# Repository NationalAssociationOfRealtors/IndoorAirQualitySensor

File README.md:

All development on the Indoor Air Quality sensor is now on its own repository [here](https://github.com/NationalAssociationOfRealtors/Touchstone).

This repo is left for historical records only.

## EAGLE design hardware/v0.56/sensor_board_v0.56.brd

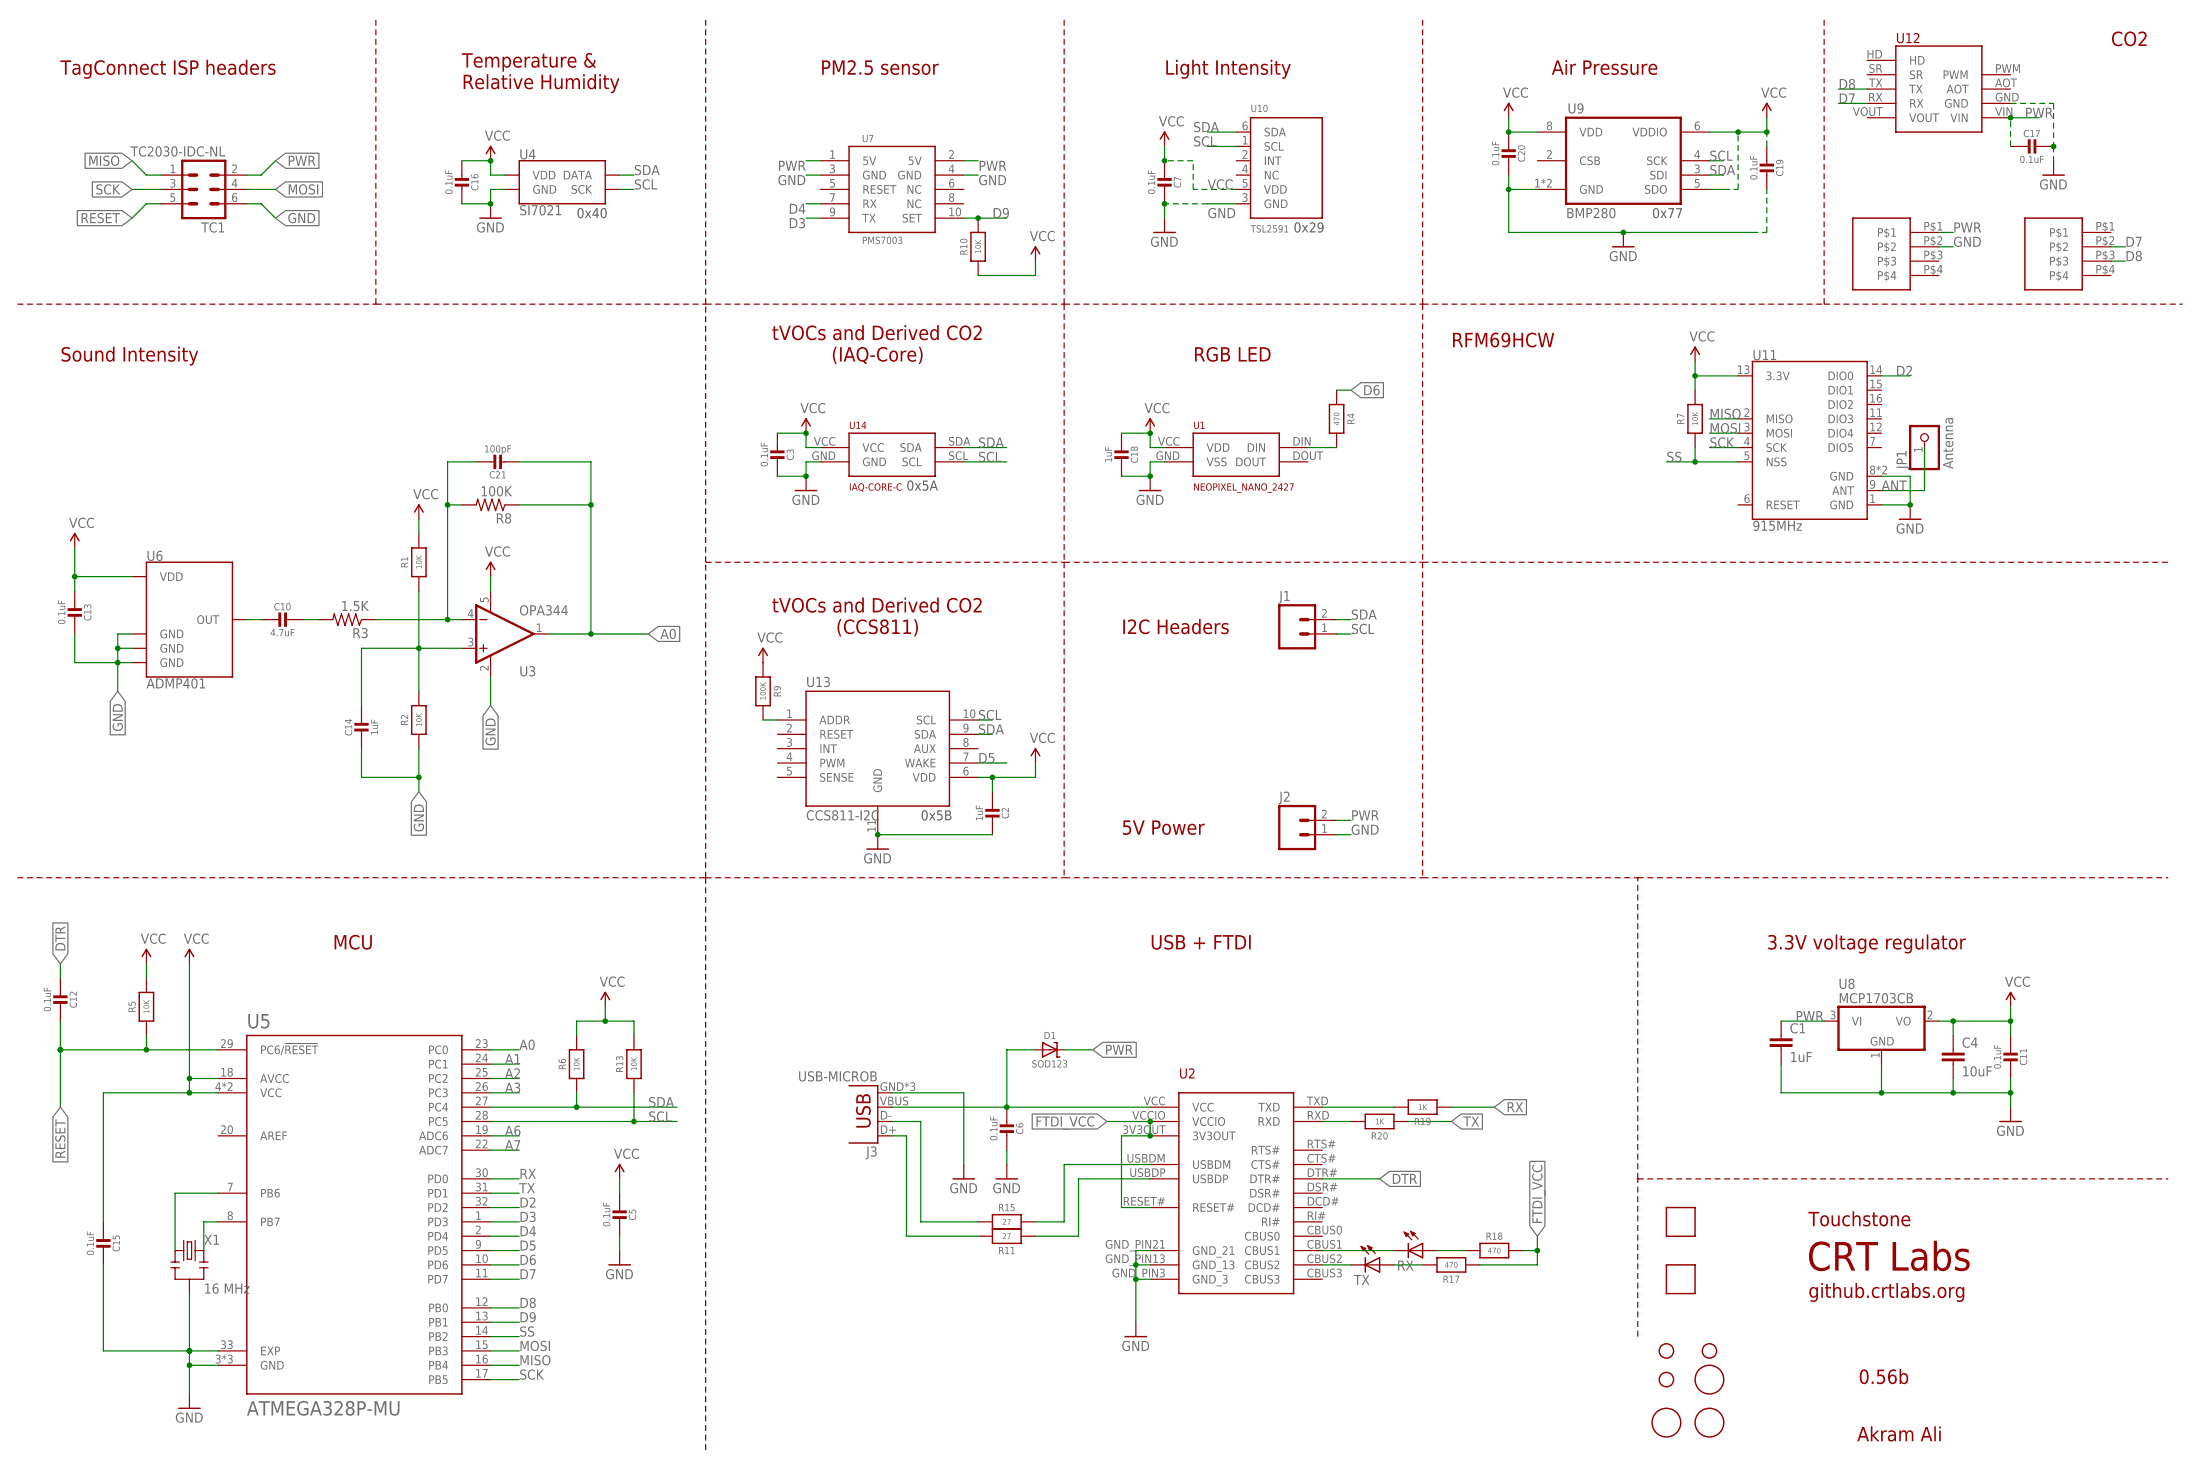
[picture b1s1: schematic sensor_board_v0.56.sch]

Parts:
C1: 1uF; 0805; MPN CC0805ZRY5V8BB105
C2, C14, C18: 1uF; MICROBUILDER__0402MP
C3, C5, C6, C7, C11, C12, C13, C15, C16, C17, C19, C20: 0.1uF; MICROBUILDER__0402MP
C4: 10uF; 0805; MPN CC0805KKX5R6BB106
C10: 4.7uF; MICROBUILDER__0402MP
C21: 100pF; MICROBUILDER__0402MP
D1: SOD123; MICROBUILDER_SOD-123
H1, H2, H3: STAND-OFF
J1, J2: M02PTH; 1X02
J3: USB-MICROB; MPN 47346-0001
JP1: Antenna; 1X01-CLEANBIG
R1, R2, R5, R6, R7, R10, R13: 10K; MICROBUILDER__0402MP
R3: 1.5K; 0805; MPN RC0805FR-071K5L
R4, R17, R18: 470; MICROBUILDER__0402MP
R8: 100K; 0805; MPN RC0805FR-07100KL
R9: 100K; MICROBUILDER__0402MP
R11, R15: 27; MICROBUILDER__0402MP
R19, R20: 1K; MICROBUILDER__0402MP
RX: LEDCHIPLED_0805; CHIPLED_0805; MPN LG R971-KN-1
TC1: TC2030-IDC-NL
TX: LEDCHIPLED_0805; CHIPLED_0805; MPN LG R971-KN-1
U1: NEOPIXEL_NANO_2427; SK6805-2427
U2: FT231XQ-R; FTDI_FT231XQ-R_PACKAGE
U3: OPA344; SOT23-5; MPN OPA344NA/3K
U4: SI7021; DFN-6-3X3-SI7021
U5: ATMEGA328P-MU; QFN50P500X500X100-33N
U6: ADMP401; MPN INMP401ACEZ-R7
U7: PMS7003; PMS7003_RECEPTACLE_1.27MM_2X5
U8: MCP1703CB; SOT23; MPN MCP1703T-2502E/CB
U9: BMP280; MPN BMP280
U10: TSL2591; DFN6_TAOS; MPN TSL25911FN
U11: 915MHz; RFM69HCW-XXXS2
U12: MH-Z19; MPN MH-z19
U13: CCS811-I2C; LGA
U14: IAQ-CORE-C
U15, U16: VLP-450-F
U$1, U$2, U$3: FIDUCIAL; FIDUCIAL_1MM
U$4, U$5: 0878980426; CONN_4POS_VERT_2.54_SMD
X1: 16 MHz; RESONATOR-SMD

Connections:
A0: C21.2, R8.1, U3.1 (OUT), U5.23 (PC0)
A1: U5.24 (PC1)
A2: U5.25 (PC2)
A3: U5.26 (PC3)
A6: U5.19 (ADC6)
A7: U5.22 (ADC7)
ANT: JP1.1, U11.9 (ANT)
D2: U5.32 (PD2), U11.14 (DIO0)
D3: U5.1 (PD3), U7.9 (TX)
D4: U5.2 (PD4), U7.7 (RX)
D5: U5.9 (PD5), U13.7 (WAKE)
D6: R4.1, U5.10 (PD6)
D7: U5.11 (PD7), U12.RX, U$5.P$2
D8: U5.12 (PB0), U12.TX, U$5.P$3
D9: R10.2, U5.13 (PB1), U7.10 (SET)
DTR: C12.2, U2.DTR#
FTDI_VCC: R17.1, R18.2, U2.3V3OUT, U2.RESET#, U2.VCCIO
GND: C1.2, C2.1, C3.1, C4.2, C5.1, C6.1, C7.1, C11.1, C13.1, C14.2, C15.1, C16.1, C17.1, C18.1, C19.1, C20.1, J2.1, J3.GND, J3.MT1 (GND), J3.MT2 (GND), R2.1, TC1.6, U1.GND (VSS), U2.GND_PIN3 (GND_3), U2.GND_PIN13 (GND_13), U2.GND_PIN21 (GND_21), U3.2 (V-), U4.GND, U5.3 (GND), U5.5 (GND), U5.21 (GND), U5.33 (EXP), U6.2 (GND), U6.4 (GND), U6.6 (GND), U7.3 (GND), U7.4 (GND), U8.1 (GND), U9.1 (GND), U9.7 (GND), U10.3 (GND), U11.1 (GND), U11.8 (GND), U11.10 (GND), U12.GND, U13.11 (GND), U14.GND, U$4.P$2, X1.2
MISO: TC1.1, U5.16 (PB4), U11.2 (MISO)
MOSI: TC1.4, U5.15 (PB3), U11.3 (MOSI)
unnamed: R4.2, U1.DIN
unnamed: R20.2, U2.RXD
unnamed: R19.2, U2.TXD
unnamed: U5.8 (PB7), X1.3
unnamed: U5.7 (PB6), X1.1
unnamed: C10.1, R3.2
unnamed: C21.1, R3.1, R8.2, U3.4 (-IN)
unnamed: C14.1, R1.1, R2.2, U3.3 (+IN)
unnamed: R9.2, U13.1 (ADDR)
unnamed: RX.C, U2.CBUS1
unnamed: TX.C, U2.CBUS2
unnamed: R15.2, U2.USBDM
unnamed: R11.1, U2.USBDP
unnamed: R18.1, RX.A
unnamed: R17.2, TX.A
unnamed: J3.D-, R15.1
unnamed: J3.D+, R11.2
OUT: C10.2, U6.1 (OUT)
PWR: C1.1, C17.2, D1.C, J2.2, TC1.2, U7.1 (5V), U7.2 (5V), U8.3 (VI), U12.VIN, U$4.P$1
RESET: C12.1, R5.1, TC1.5, U5.29 (PC6/!RESET)
RX: R19.1, U5.30 (PD0)
SCK: TC1.3, U5.17 (PB5), U11.4 (SCK)
SCL: J1.1, R13.1, U4.SCK, U5.28 (PC5), U9.4 (SCK), U10.1 (SCL), U13.10 (SCL), U14.SCL
SDA: J1.2, R6.1, U4.DATA, U5.27 (PC4), U9.3 (SDI), U10.6 (SDA), U13.9 (SDA), U14.SDA
SS: R7.1, U5.14 (PB2), U11.5 (NSS)
TX: R20.1, U5.31 (PD1)
VBUS: C6.2, D1.A, J3.VBUS, U2.VCC
VCC: C2.2, C3.2, C4.1, C5.2, C7.2, C11.2, C13.2, C15.2, C16.2, C18.2, C19.2, C20.2, R1.2, R5.2, R6.2, R7.2, R9.1, R10.1, R13.2, U1.VCC (VDD), U3.5 (V+), U4.VDD, U5.4 (VCC), U5.6 (VCC), U5.18 (AVCC), U6.5 (VDD), U8.2 (VO), U9.5 (SDO), U9.6 (VDDIO), U9.8 (VDD), U10.5 (VDD), U11.13 (3.3V), U13.6 (VDD), U14.VCC

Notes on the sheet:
Light Intensity
tVOCs and Derived CO2 (IAQ-Core)
Air Pressure
Sound Intensity
Temperature & Relative Humidity
TagConnect ISP headers
3.3V voltage regulator
CRT Labs
Touchstone
Akram Ali
USB + FTDI
0x5A
0x77
0.56b
github.crtlabs.org
0x29
RGB LED
I2C Headers
PM2.5 sensor
RFM69HCW
MCU
CO2
tVOCs and Derived CO2 (CCS811)
5V Power
0x5B
0x40

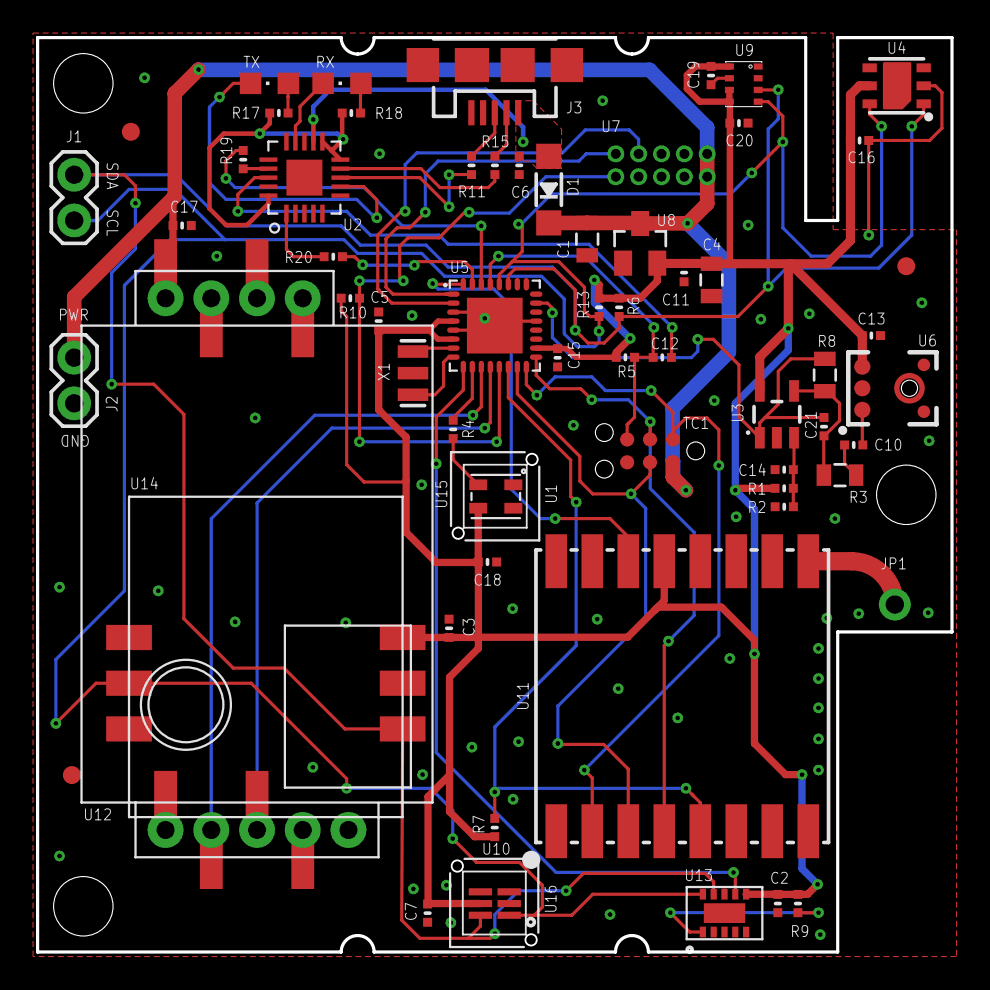
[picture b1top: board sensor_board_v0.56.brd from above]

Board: 2 copper layers, 50.8 x 50.8 mm, 69 parts (1 on the bottom side), 43 nets.

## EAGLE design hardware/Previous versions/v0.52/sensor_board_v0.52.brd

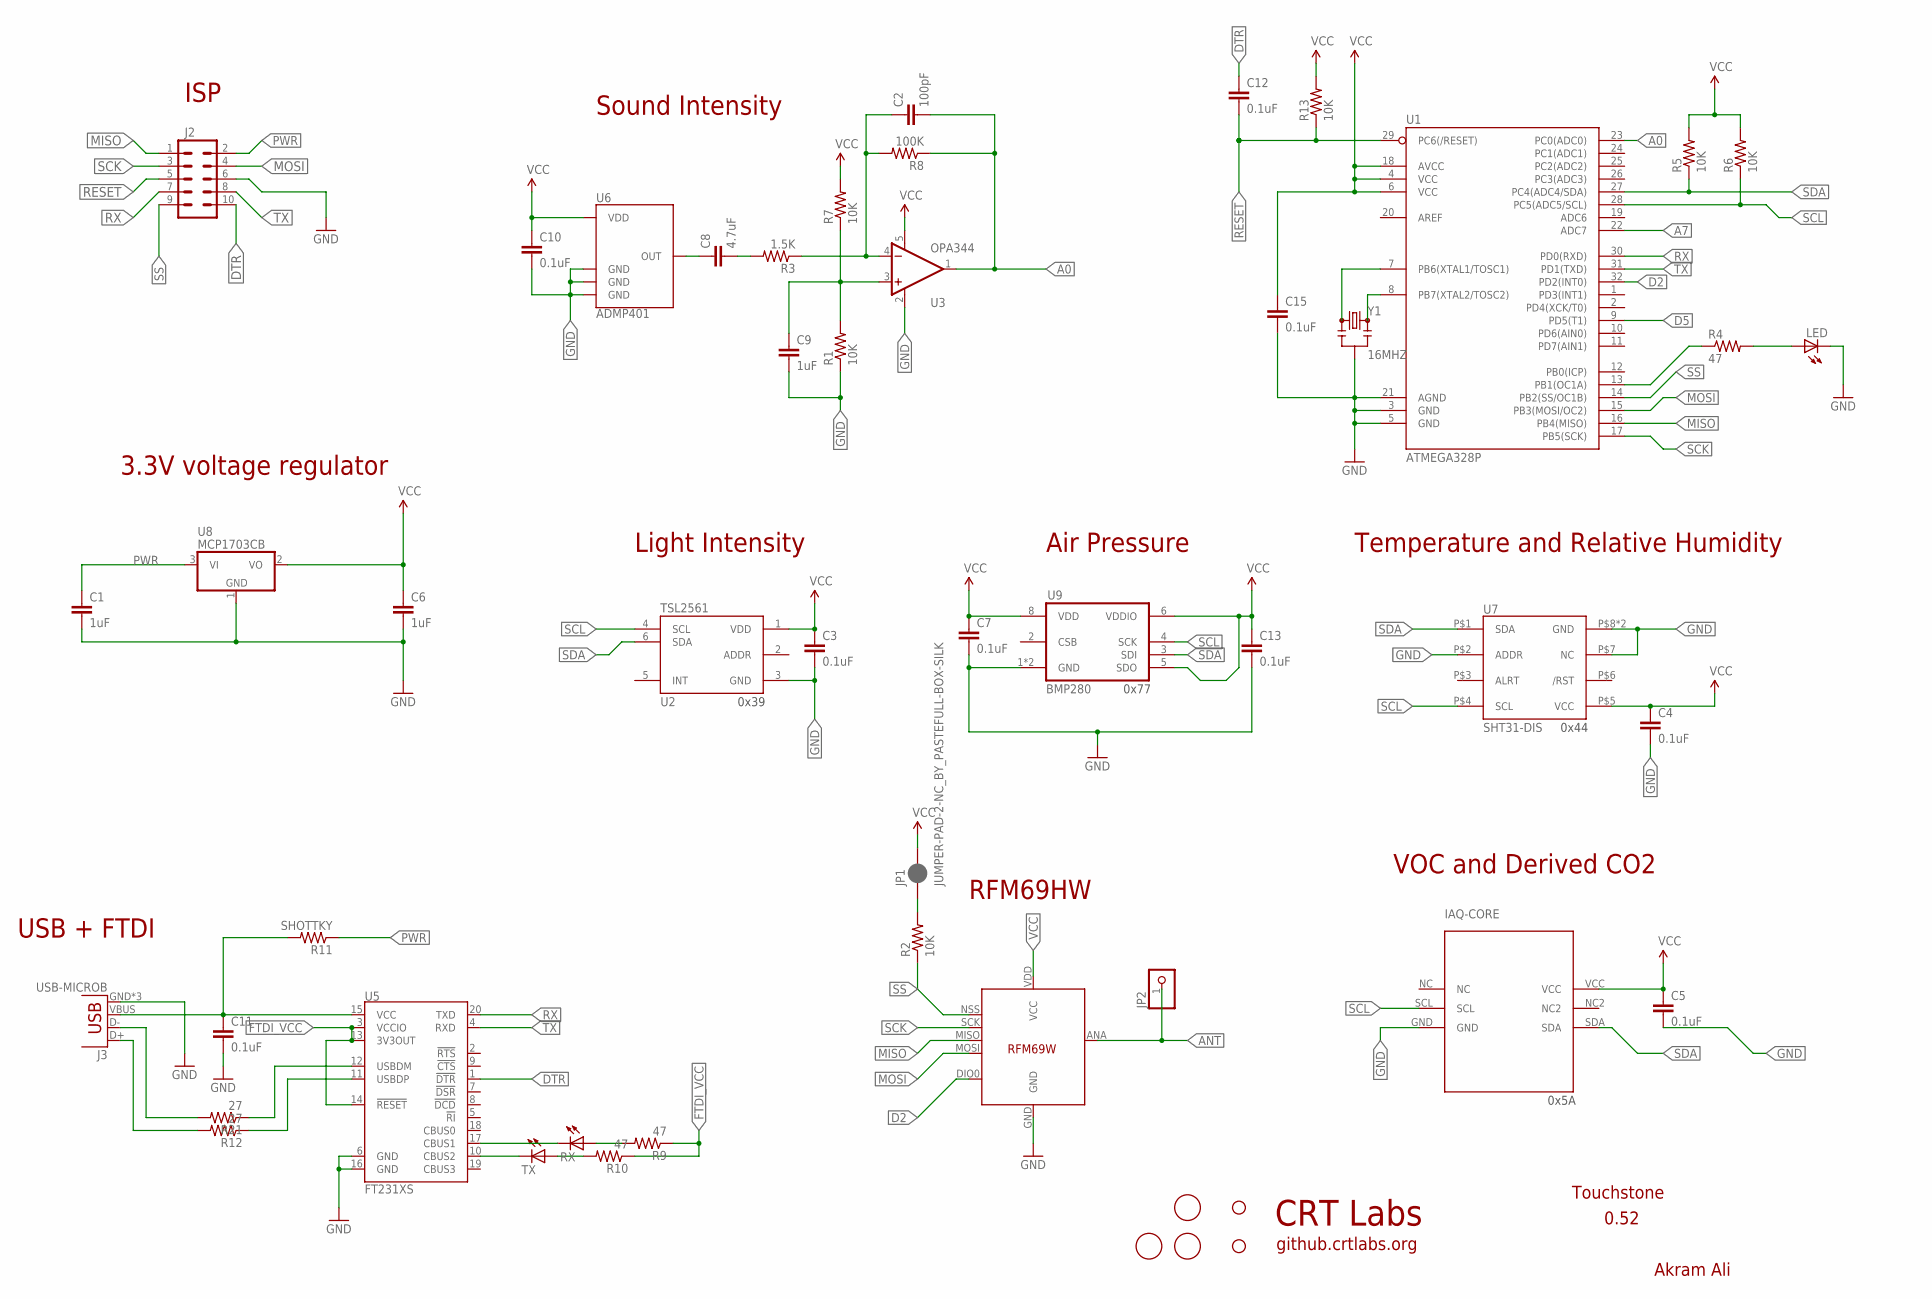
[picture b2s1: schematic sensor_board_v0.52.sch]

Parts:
C1, C6, C9: 1uF; 0805
C2: 100pF; 0805
C3, C4, C5, C7, C10, C11, C12, C13, C15: 0.1uF; 0805
C8: 4.7uF; 0805
H1, H2: STAND-OFF
IAQ-CORE: IAQ-CORE; MPN IAQ CORE
J2: M05X2PTH; AVR_ICSP
J3: USB-MICROB
JP1: JUMPER-PAD-2-NC_BY_PASTEFULL-BOX-SILK; PAD-JUMPER-2-NC_BY_PASTE_YES_SILK_FULL_BOX
JP2: PINHD-1X1; 1X01
LED: LEDCHIPLED_0805; CHIPLED_0805
R1, R2, R5, R6, R7, R13: 10K; 0805
R3: 1.5K; 0805
R4, R9, R10: 47; 0805
R8: 100K; 0805
R11: SHOTTKY; 0805
R12, R21: 27; 0805
RX: LEDCHIPLED_0805; CHIPLED_0805
TX: LEDCHIPLED_0805; CHIPLED_0805
U1: ATMEGA328P; TQFP32-08; MPN ATMEGA328PB-AU
U2: TSL2561; FN-6; MOUSER# 856-TSL2561T; DIGIKEY# TSL2561-FNCT-ND
U3: OPA344; SOT23-5
U4: RFM69HW; LOWPOWERLAB_RFM69W-MINPADS
U5: FT231XS; SSOP20_L
U6: ADMP401
U7: SHT31-DIS; SHT3X; MPN SHT31-DIS-B
U8: MCP1703CB; SOT23; MPN MCP1703T-2502E/CB
U9: BMP280
U$1, U$2, U$3: FIDUCIAL; FIDUCIAL_1MM
Y1: 16MHZ; RESONATOR-SMD

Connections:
A0: C2.2, R8.1, U1.23 (PC0(ADC0)), U3.1 (OUT)
A7: U1.22 (ADC7)
ANT: JP2.1, U4.ANA (ANT)
D2: U1.32 (PD2(INT0)), U4.DIO0
D5: U1.9 (PD5(T1))
DTR: C12.1, J2.10, U5.1 (!DTR)
FTDI_VCC: R9.1, R10.1, U5.3 (VCCIO), U5.13 (3V3OUT), U5.14 (!RESET)
GND: C1.2, C3.2, C4.2, C5.2, C6.2, C7.2, C9.2, C10.2, C11.2, C13.2, C15.2, IAQ-CORE.GND, J2.6, J3.GND, J3.MT1 (GND), J3.MT2 (GND), LED.C, R1.1, U1.3 (GND), U1.5 (GND), U1.21 (AGND), U2.3 (GND), U3.2 (V-), U4.GND, U5.6 (GND), U5.16 (GND), U6.2 (GND), U6.4 (GND), U6.6 (GND), U7.P$2 (ADDR), U7.P$7 (NC), U7.P$8 (GND), U7.PAD (GND), U8.1 (GND), U9.1 (GND), U9.7 (GND), Y1.2
MISO: J2.1, U1.16 (PB4(MISO)), U4.MISO
MOSI: J2.4, U1.15 (PB3(MOSI/OC2)), U4.MOSI
unnamed: JP1.1, R2.2
unnamed: R4.1, U1.13 (PB1(OC1A))
unnamed: LED.A, R4.2
unnamed: U1.8 (PB7(XTAL2/TOSC2)), Y1.3
unnamed: U1.7 (PB6(XTAL1/TOSC1)), Y1.1
unnamed: C8.2, R3.2
unnamed: C2.1, R3.1, R8.2, U3.4 (-IN)
unnamed: C9.1, R1.2, R7.1, U3.3 (+IN)
unnamed: RX.C, U5.17 (CBUS1)
unnamed: TX.C, U5.10 (CBUS2)
unnamed: R21.1, U5.12 (USBDM)
unnamed: R12.1, U5.11 (USBDP)
unnamed: R9.2, RX.A
unnamed: R10.2, TX.A
unnamed: J3.D-, R21.2
unnamed: J3.D+, R12.2
OUT: C8.1, U6.1 (OUT)
PWR: C1.1, J2.2, R11.1, U8.3 (VI)
RESET: C12.2, J2.5, R13.1, U1.29 (PC6(/RESET))
RX: J2.7, U1.30 (PD0(RXD)), U5.20 (TXD)
SCK: J2.3, U1.17 (PB5(SCK)), U4.SCK
SCL: IAQ-CORE.SCL, R6.1, U1.28 (PC5(ADC5/SCL)), U2.4 (SCL), U7.P$4 (SCL), U9.4 (SCK)
SDA: IAQ-CORE.SDA, R5.1, U1.27 (PC4(ADC4/SDA)), U2.6 (SDA), U7.P$1 (SDA), U9.3 (SDI)
SS: J2.9, R2.1, U1.14 (PB2(SS/OC1B)), U4.NSS (SEL)
TX: J2.8, U1.31 (PD1(TXD)), U5.4 (RXD)
VBUS: C11.1, J3.VBUS, R11.2, U5.15 (VCC)
VCC: C3.1, C4.1, C5.1, C6.1, C7.1, C10.1, C13.1, C15.1, IAQ-CORE.VCC, JP1.2, R5.2, R6.2, R7.2, R13.2, U1.4 (VCC), U1.6 (VCC), U1.18 (AVCC), U2.1 (VDD), U3.5 (V+), U4.VDD (VCC), U6.5 (VDD), U7.P$5 (VCC), U8.2 (VO), U9.5 (SDO), U9.6 (VDDIO), U9.8 (VDD)

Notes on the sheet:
Light Intensity
VOC and Derived CO2
Air Pressure
Sound Intensity
Temperature and Relative Humidity
ISP
3.3V voltage regulator
CRT Labs
Touchstone
Akram Ali
RFM69HW
USB + FTDI
0x39
0x5A
0x44
0x77
0.52
github.crtlabs.org

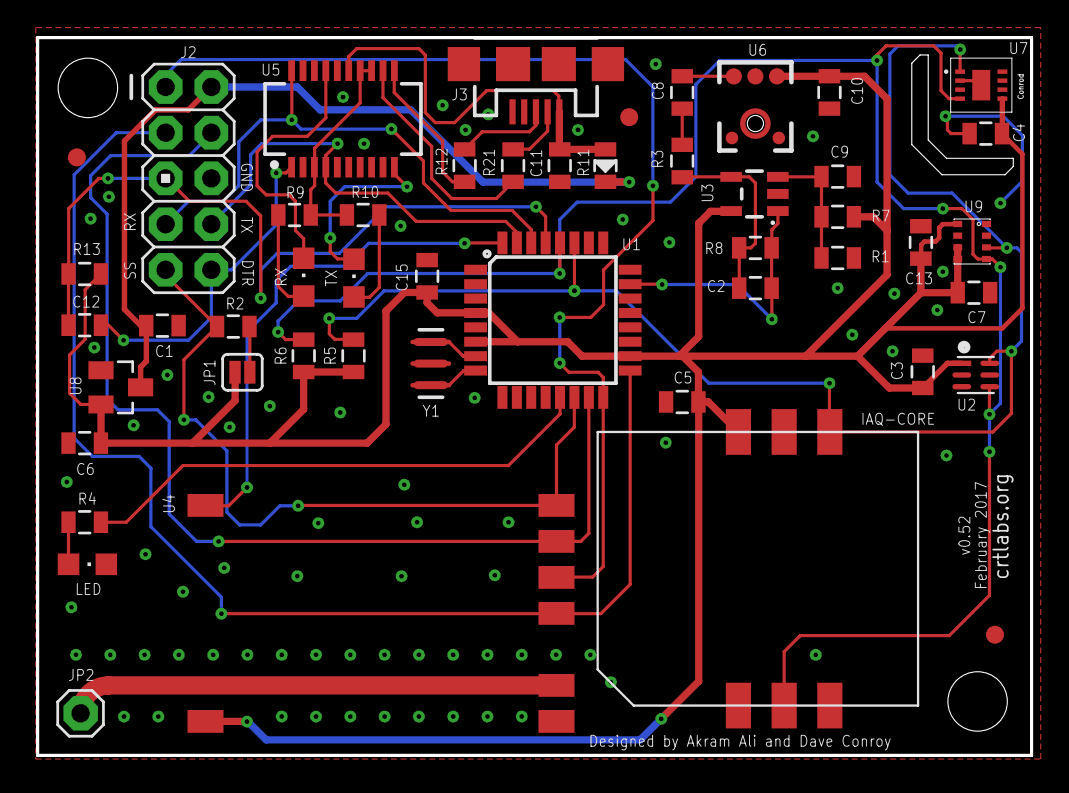
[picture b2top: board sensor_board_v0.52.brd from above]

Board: 2 copper layers, 55.2 x 39.9 mm, 51 parts (0 on the bottom side), 35 nets.

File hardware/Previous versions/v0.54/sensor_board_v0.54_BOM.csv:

Qty,Value,Device,Package,Parts,Description,MPN
1,USB-MICROB,USB-MICROB,USB-MICROB,J3,USB Connectors,47346-0001
1,ATMEGA328P,ATMEGA328P_TQFP,TQFP32-08,U1,ATMEGA328P,ATMEGA328PB-AU
1,BMP280,BMP280,BMP280,U9,The BMP280 is an absolute barometric pressure sensor especially designed for mobile applications. The sensor module is housed in an extremely compact 8-pin metal-lid LGA package with a footprint of only 2.0 ÌÑ 2.5 mm2 and 0.95 mm package height. Its small,BMP280
1,100pF,CAP0805,805,C2,Capacitor,CC0805JRNPOABN101
1,10uF,CAP0805,805,C4,Capacitor,CC0805KKX5R6BB106
1,4.7uF,CAP0805,805,C8,Capacitor,CC0805KKX7R6BB475
10,0.1uF,CAP0805,805,C5-C6-C7-C10-C11-C12-C13-C14-C15-C16,Capacitor,CC0805KRX7R9BB104
3,1uF,CAP0805,805,C1-C3-C9,Capacitor,CC0805ZRY5V8BB105
1,16MHZ,RESONATOR16MHZ,RESONATOR-SMD,Y1,Resonator,CSTCE16M0V53-R0
1,FT231XS,FT231XS,SSOP20_L,U5,FTDI FT231X Full Speed USB to Full-handshake UART,FT231XQ-R
1,IAQ-CORE,IAQ-CORE,IAQ-CORE,IAQ-CORE,IAQ-CORE,IAQ-CORE C
1,ADMP401,ADMP401,ADMP401,U6,Omnidirection bottom-port MEMS microphone,INMP401ACEZ-R7
2,,LEDCHIPLED_0805,CHIPLED_0805,RX- TX,LED,LG R971-KN-1
1,MCP1703CB,MCP1703CB,SOT23,U8,250 mA- 16V- Low Quiescent Current LDO Regulator,MCP1703T-2502E/CB
1,OPA344,OPA344,SOT23-5,U3,Single gate rail-to-rail output op-amp. Inputs extend 300mV past rails.,OPA344NA/3K
1,100K,RESISTOR0805-RES,805,R8,Resistor,RC0805FR-07100KL 
6,10K,RESISTOR0805-RES,805,R1-R2-R5-R6-R7-R13,Resistor,RC0805FR-0710KL
1,1.5K,RESISTOR0805-RES,805,R3,Resistor,RC0805FR-071K5L 
2,1K,RESISTOR0805-RES,805,R4-R14,Resistor,RC0805FR-071KL
2,27,RESISTOR0805-RES,805,R12-R21,Resistor,RC0805FR-0727RL 
1,470,R-US_R0603,R0603,R16,RESISTOR- American symbol,RC0805FR-07470RL 
2,47,RESISTOR0805-RES,805,R9-R10,Resistor,RC0805FR-0747RL 
1,RFM69HW,LOWPOWERLAB_RFM69,LOWPOWERLAB_RFM69W-MINPADS,U4,RFM Radio,RFM69HW
1,SHOTTKY,RESISTOR0805-RES,805,R11,Resistor,SD0805S040S0R5
1,SHT35,SHT3X,SHT3X,U2,SHT3x - Digital Temperature and Humidity Sensor,SHT35-DIS-B
1,WS2812B3535,WS2812B3535,LED3535,LED1,LED,SK6812 mini
1,TSL2591,LIGHT_TSL2591,DFN6_TAOS,U10,TSL2591 Light-To-Digital Sensor,TSL25911FN

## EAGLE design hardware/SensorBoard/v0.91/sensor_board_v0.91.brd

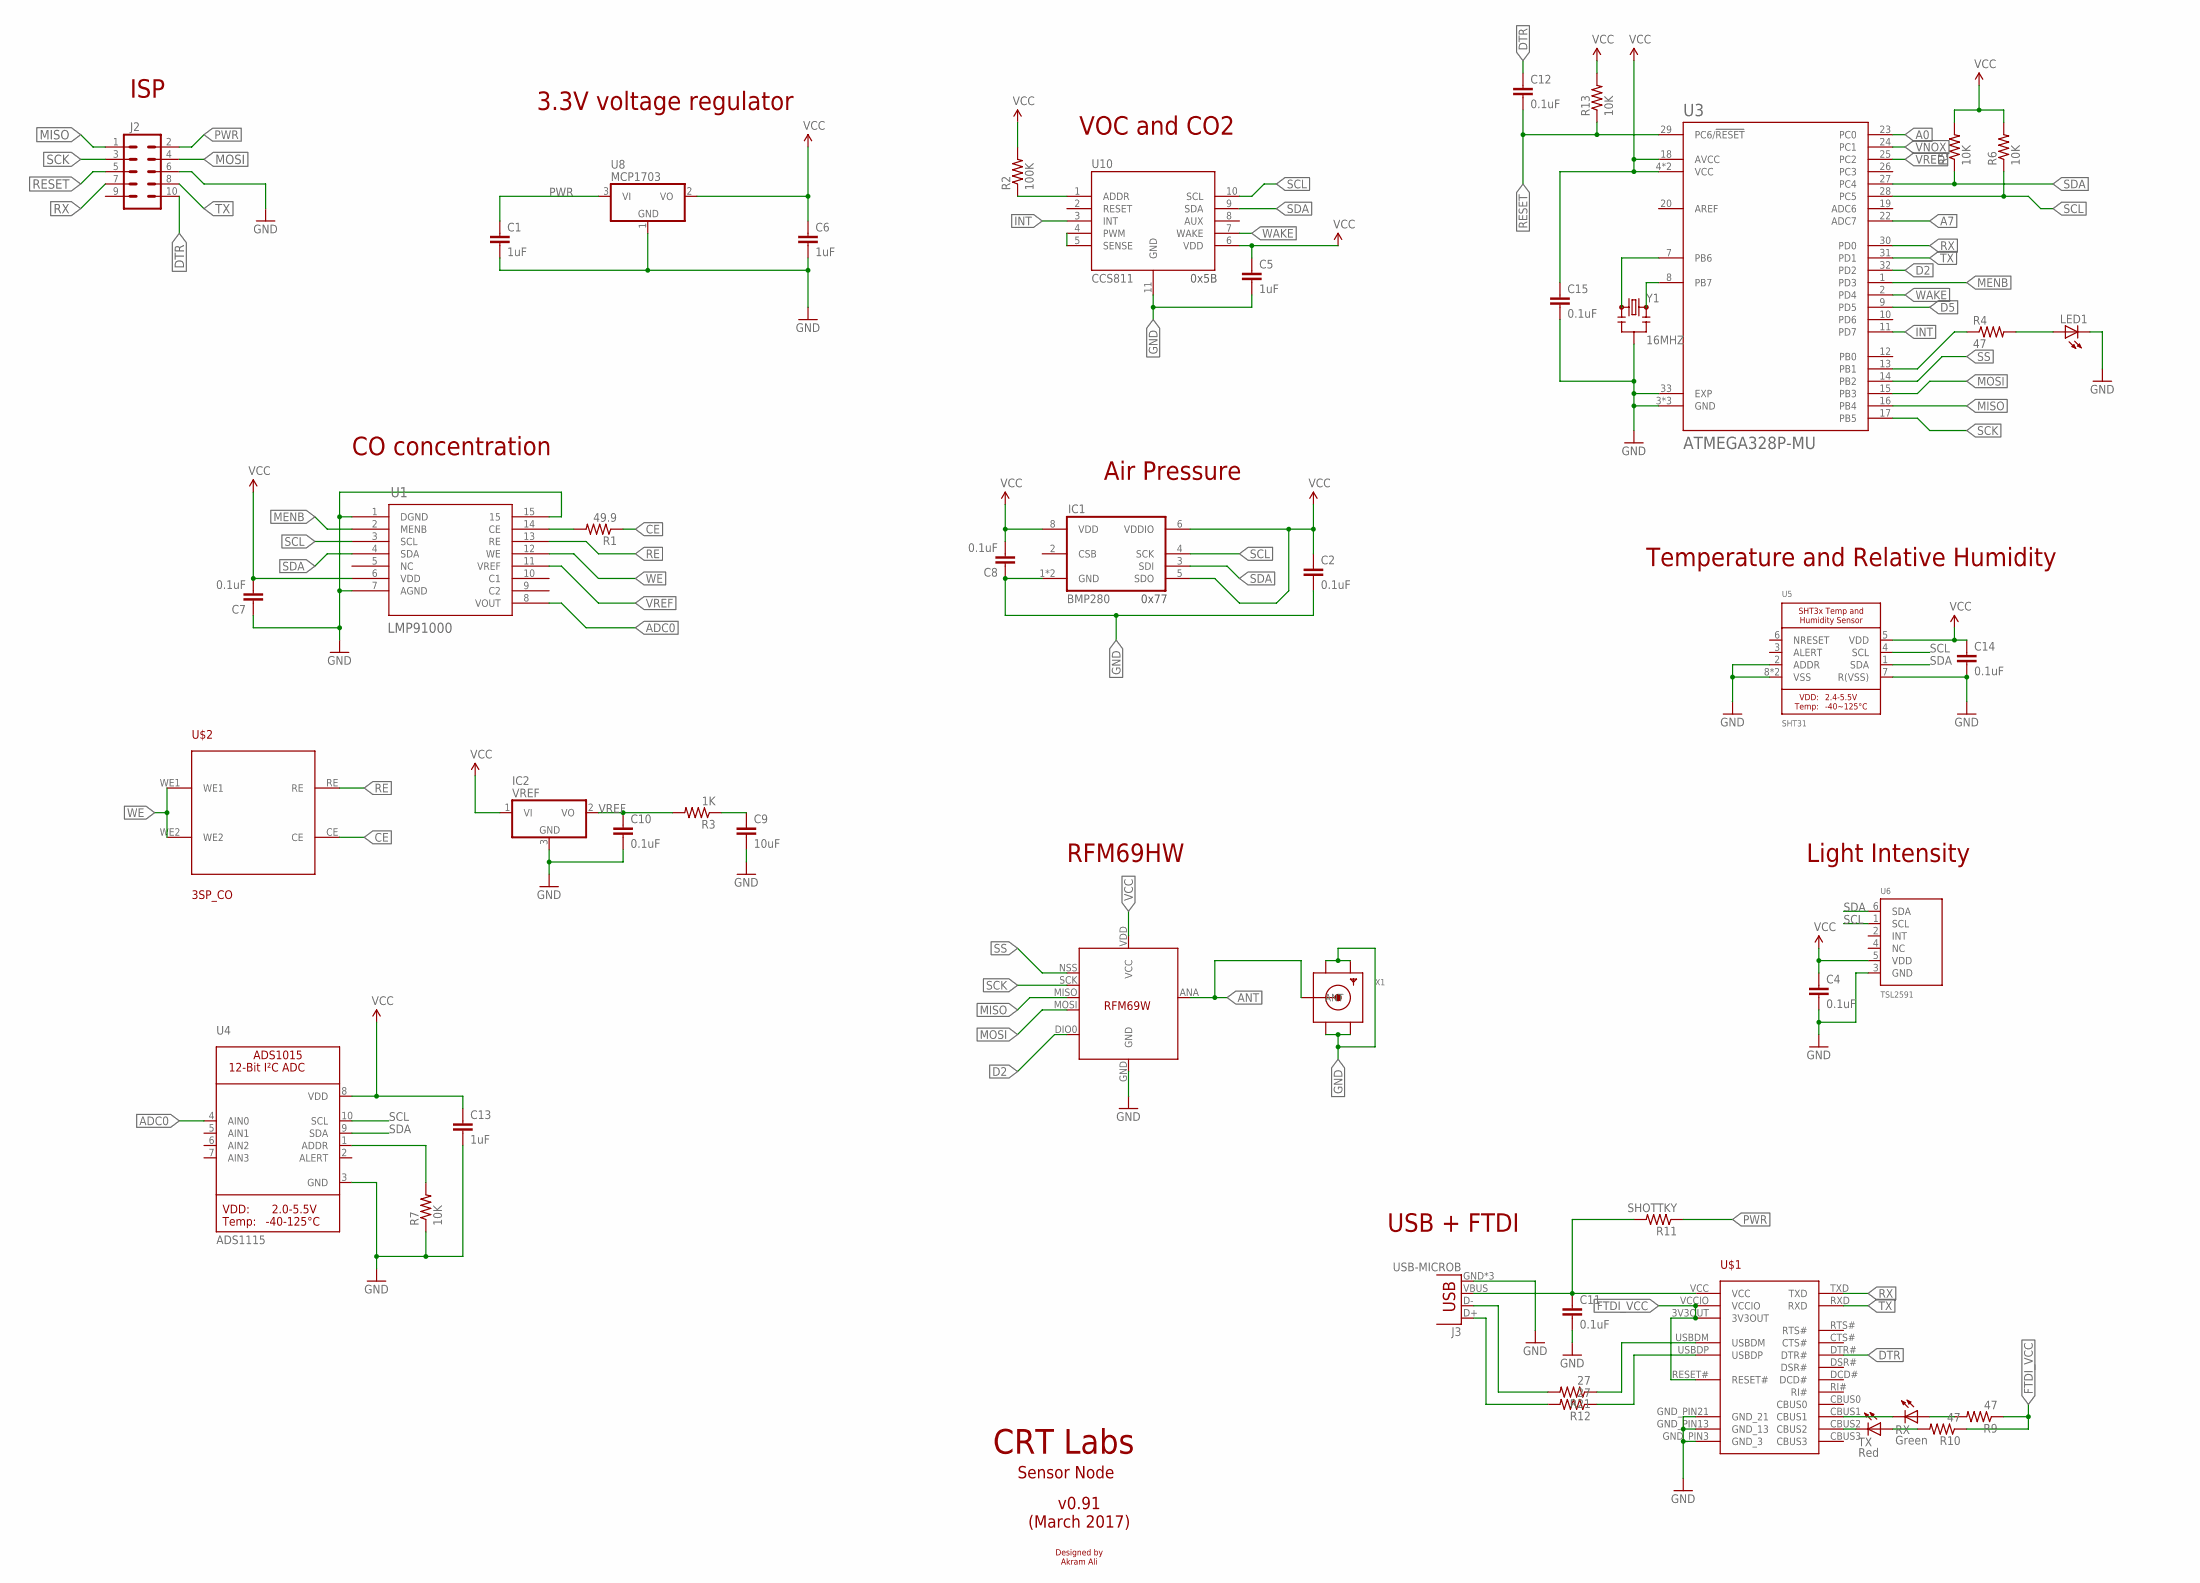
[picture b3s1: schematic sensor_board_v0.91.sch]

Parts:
C1, C5, C6, C13: 1uF; 0805; MPN CC0805KKX7R7BB105
C2, C4, C7, C8, C10, C11, C12, C14, C15: 0.1uF; 0805; MPN AC0805KRX7R9BB104
C9: 10uF; 0805; MPN CC0805ZKY5V6BB106
IC1: BMP280; MPN BMP280
IC2: VREF; SOT23; MPN ISL60002DIH320Z-TK
J2: M05X2PTH; AVR_ICSP
J3: USB-MICROB; MPN CONN-09505
LED1: LEDCHIPLED_0805; CHIPLED_0805; MPN 150080BS75000
R1: 49.9; 0805; MPN RC0805FR-0749R9L
R2: 100K; 0805; MPN 311-100KCRCT-ND
R3: 1K; 0805; MPN RC0805JR-071KL
R4, R9, R10: 47; 0805; MPN RC0805JR-0747RL
R5, R6, R7, R13: 10K; 0805; MPN RC0805JR-0710KL
R11: SHOTTKY; 0805; MPN SD0805S020S0R5
R12, R21: 27; 0805; MPN RC0805FR-0727RL
RX: Green; CHIPLED_0805; MPN LG R971-KN-1
TX: Red; CHIPLED_0805; MPN LH R974-LP-1
U1: LMP91000; SDA14B; MPN LMP91000
U3: ATMEGA328P-MU; QFN50P500X500X100-33N; MPN ATMEGA328P-MU
U4: ADS1115; MSOP10
U5: SHT31; SHT3X
U6: TSL2591; DFN6_TAOS
U8: MCP1703; SOT23; MPN MCP1703T-2502E/CB
U10: CCS811; LGA; MPN CCS811
U11: RFM69HW; LOWPOWERLAB_RFM69W-MINPADS; MPN RFM69HW
U$1: FT231XQ-R; FTDI_FT231XQ-R_PACKAGE; MPN FT231XQ-R
U$2: 3SP_CO; 3SP_CO_PIN_PACKAGE; MPN 3SP CO
X1: SMACONNECTOR_EDGE; SMA_EDGELAUNCH; MPN WRL-00593
Y1: 16MHZ; RESONATOR-SMD; MPN CSTCE16M0V53-R0

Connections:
A0: U3.23 (PC0)
A7: U3.22 (ADC7)
ADC0: U1.8 (VOUT), U4.4 (AIN0)
ANT: U11.ANA (ANT), X1.P (ANT)
CE: R1.1, U$2.CE
D2: U3.32 (PD2), U11.DIO0
D5: U3.9 (PD5)
DTR: C12.1, J2.10, U$1.DTR#
FTDI_VCC: R9.1, R10.1, U$1.3V3OUT, U$1.RESET#, U$1.VCCIO
GND: C1.2, C2.2, C4.2, C5.2, C6.2, C7.1, C8.1, C9.2, C10.2, C11.2, C13.2, C14.2, C15.2, IC1.1 (GND), IC1.7 (GND), IC2.3 (GND), J2.6, J3.GND, J3.MT1 (GND), J3.MT2 (GND), LED1.C, R7.1, U1.1 (DGND), U1.7 (AGND), U1.15, U3.3 (GND), U3.5 (GND), U3.21 (GND), U3.33 (EXP), U4.3 (GND), U5.2 (ADDR), U5.7 (R(VSS)), U5.8 (VSS), U5.THERMAL (VSS), U6.3 (GND), U8.1 (GND), U10.11 (GND), U11.GND, U$1.GND_PIN3 (GND_3), U$1.GND_PIN13 (GND_13), U$1.GND_PIN21 (GND_21), X1.GND@1 (GND4), X1.GND@2 (GND3), X1.GND@3 (GND2), X1.GND@4 (GND1), Y1.2
INT: U3.11 (PD7), U10.3 (INT)
MENB: U1.2 (MENB), U3.1 (PD3)
MISO: J2.1, U3.16 (PB4), U11.MISO
MOSI: J2.4, U3.15 (PB3), U11.MOSI
unnamed: R2.1, U10.1 (ADDR)
unnamed: R4.1, U3.13 (PB1)
unnamed: LED1.A, R4.2
unnamed: U3.8 (PB7), Y1.3
unnamed: U3.7 (PB6), Y1.1
unnamed: U10.4 (PWM), U10.5 (SENSE)
unnamed: R1.2, U1.14 (CE)
unnamed: C9.1, R3.1
unnamed: R7.2, U4.1 (ADDR)
unnamed: RX.C, U$1.CBUS1
unnamed: TX.C, U$1.CBUS2
unnamed: R21.1, U$1.USBDM
unnamed: R12.1, U$1.USBDP
unnamed: R9.2, RX.A
unnamed: R10.2, TX.A
unnamed: J3.D-, R21.2
unnamed: J3.D+, R12.2
PWR: C1.1, J2.2, R11.1, U8.3 (VI)
RE: U1.13 (RE), U$2.RE
RESET: C12.2, J2.5, R13.1, U3.29 (PC6/!RESET)
RX: J2.7, U3.30 (PD0), U$1.TXD
SCK: J2.3, U3.17 (PB5), U11.SCK
SCL: IC1.4 (SCK), R6.1, U1.3 (SCL), U3.28 (PC5), U4.10 (SCL), U5.4 (SCL), U6.1 (SCL), U10.10 (SCL)
SDA: IC1.3 (SDI), R5.1, U1.4 (SDA), U3.27 (PC4), U4.9 (SDA), U5.1 (SDA), U6.6 (SDA), U10.9 (SDA)
SS: U3.14 (PB2), U11.NSS (SEL)
TX: J2.8, U3.31 (PD1), U$1.RXD
VBUS: C11.1, J3.VBUS, R11.2, U$1.VCC
VCC: C2.1, C4.1, C5.1, C6.1, C7.2, C8.2, C13.1, C14.1, C15.1, IC1.5 (SDO), IC1.6 (VDDIO), IC1.8 (VDD), IC2.1 (VI), R2.2, R5.2, R6.2, R13.2, U1.6 (VDD), U3.4 (VCC), U3.6 (VCC), U3.18 (AVCC), U4.8 (VDD), U5.5 (VDD), U6.5 (VDD), U8.2 (VO), U10.6 (VDD), U11.VDD (VCC)
VNOX: U3.24 (PC1)
VRED: U3.25 (PC2)
VREF: C10.1, IC2.2 (VO), R3.2, U1.11 (VREF)
WAKE: U3.2 (PD4), U10.7 (WAKE)
WE: U1.12 (WE), U$2.WE1, U$2.WE2

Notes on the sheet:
Light Intensity
VOC and CO2
Air Pressure
Temperature and Relative Humidity
ISP
3.3V voltage regulator
CRT Labs
Sensor Node
v0.91 (March 2017)
Designed by Akram Ali
RFM69HW
USB + FTDI
0x5B
0x77
CO concentration

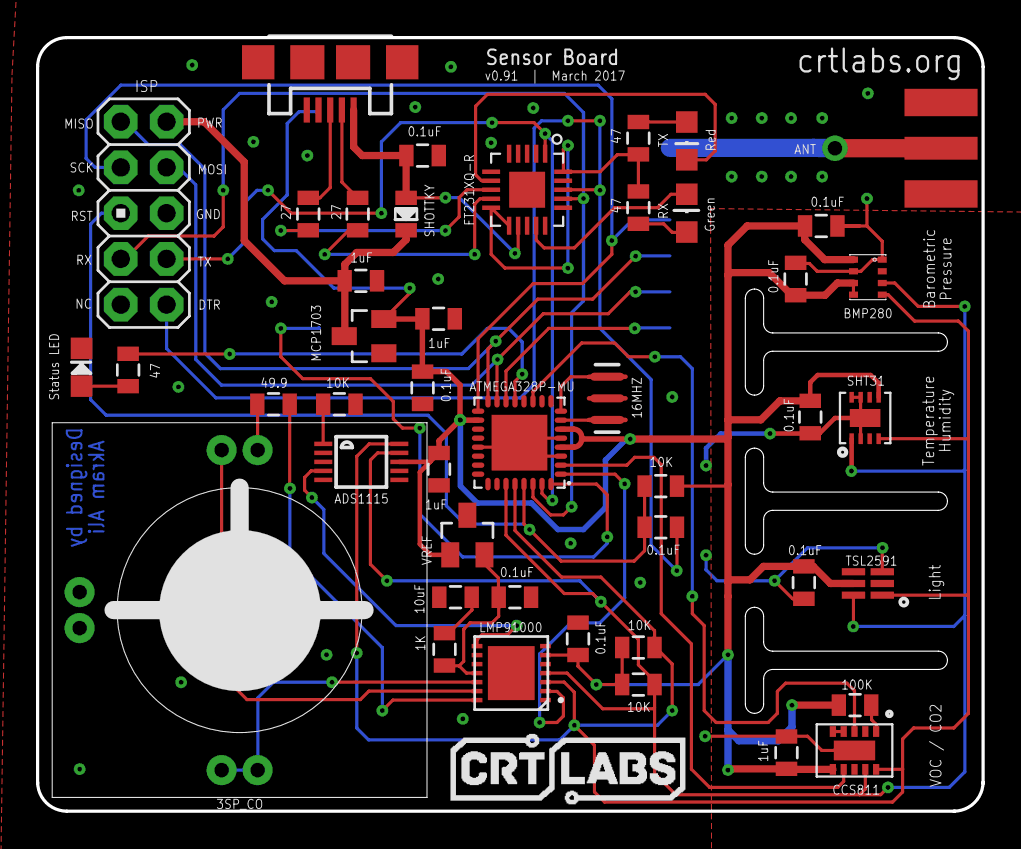
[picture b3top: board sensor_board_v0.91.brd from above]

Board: 2 copper layers, 52.5 x 43.0 mm, 46 parts (1 on the bottom side), 42 nets.

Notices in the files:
parts and their libraries:
microbuilder: This work is placed in the public domain, and may be freely used for commercial and non-commercial work with the following conditions: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
SparkFun-DigitalIC: Licensing: Creative Commons ShareAlike 4.0 International - https://creativecommons.org/licenses/by-sa/4.0
